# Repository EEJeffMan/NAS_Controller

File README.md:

# NAS_Controller
This is a PCB that serves as a controller for power supplies and provides power/reset control for a Pi-based NAS.

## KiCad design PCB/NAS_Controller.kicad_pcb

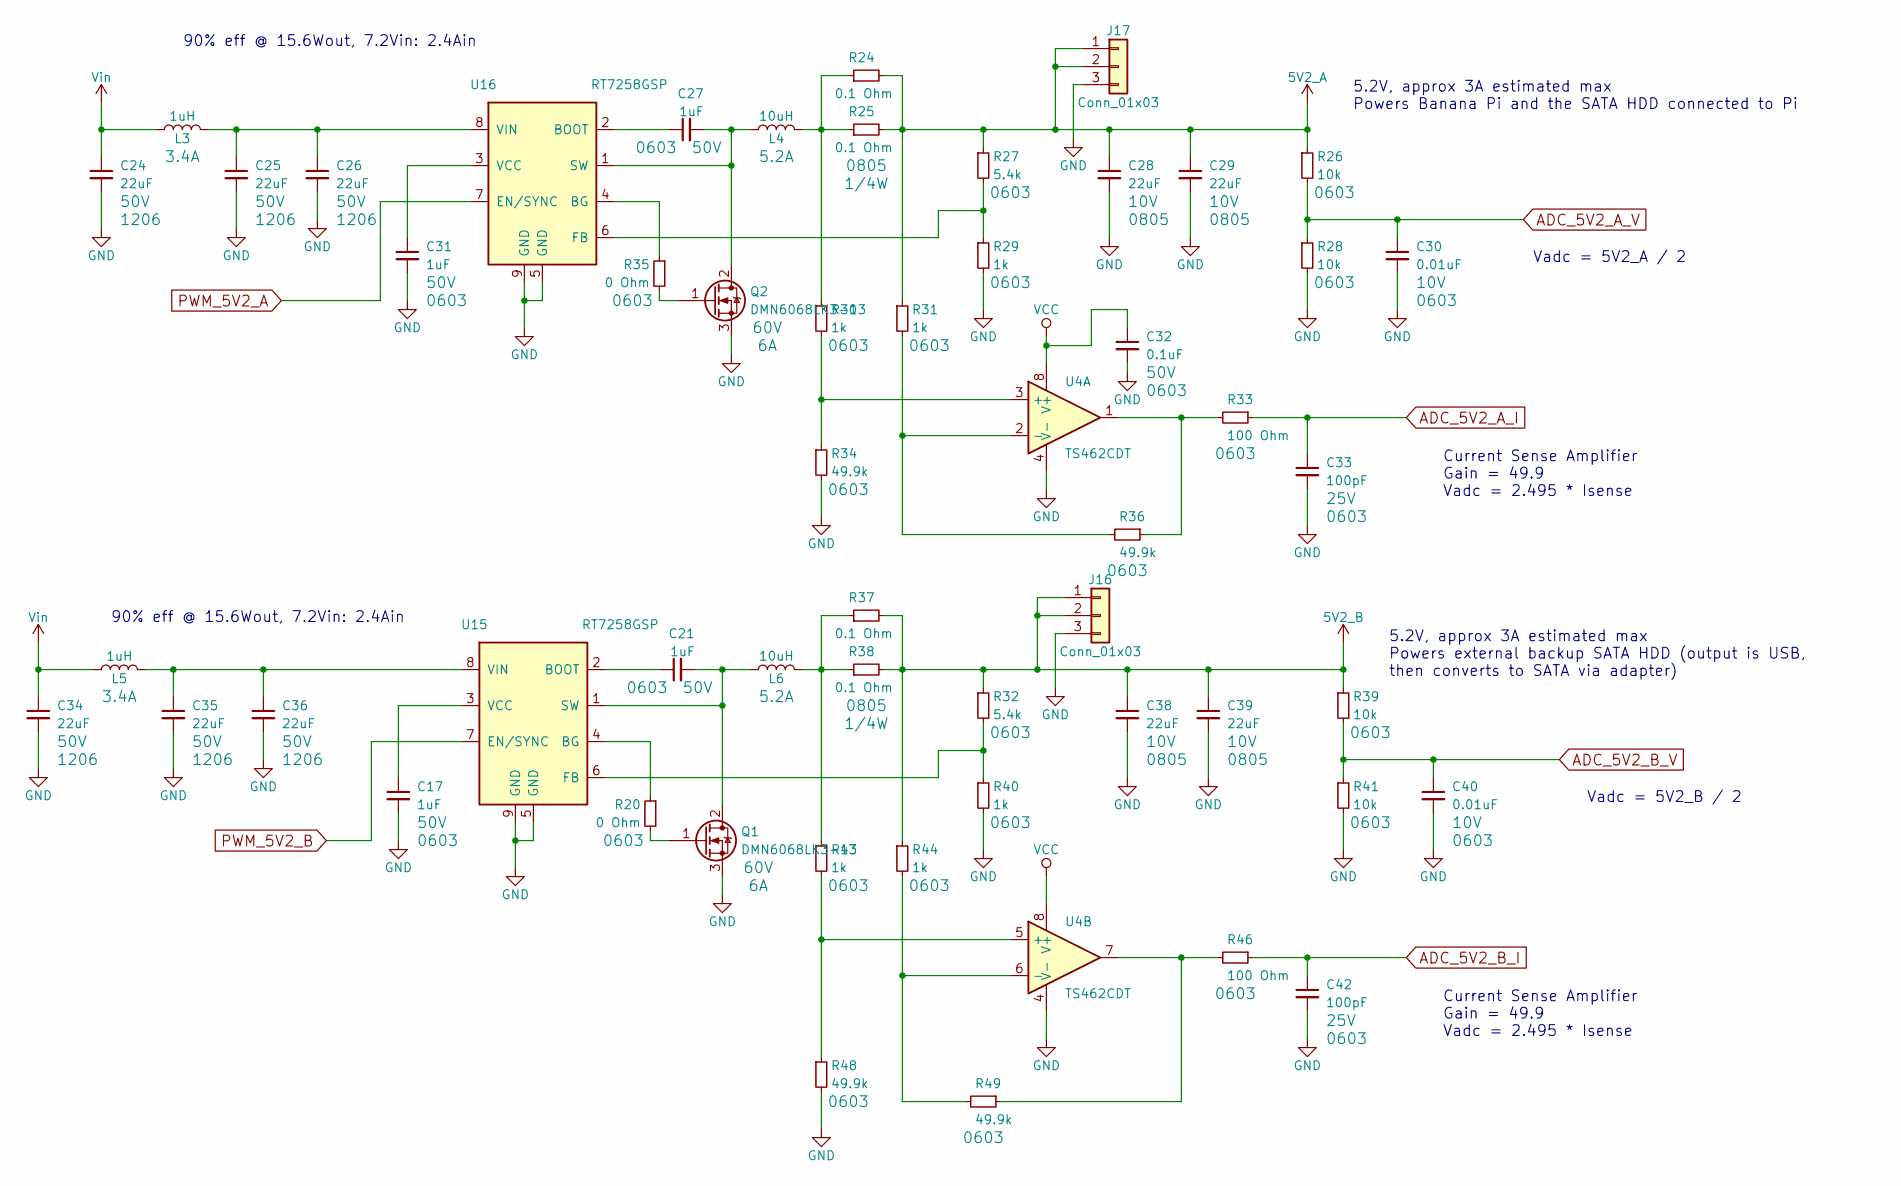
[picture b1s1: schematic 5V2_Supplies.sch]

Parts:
C17, C21, C27, C31: 1uF; C_0603; Voltage 50V
C24, C25, C26, C34, C35, C36: 22uF; C_1206; Voltage 50V
C28, C29, C38, C39: 22uF; C_0805; Voltage 10V
C30, C40: 0.01uF; C_0603; Voltage 10V
C32: 0.1uF; C_0603; Voltage 50V
C33, C42: 100pF; C_0603; Voltage 25V
J16, J17: Conn_01x03; Pin_Header_Straight_1x03_Pitch2.54mm_SMD_Pin1Right
L3, L5: 1uH; INDP2622X120N
L4, L6: 10uH; Inductor_Taiyo-Yuden_NR-80xx_HandSoldering
Q1, Q2: DMN6068LK3-13; TO-252-2; Voltage 60V
R20, R35: 0 Ohm; R_0603
R24, R25, R37, R38: 0.1 Ohm; R_0805
R26, R28, R39, R41: 10k; R_0603
R27, R32: 5.4k; R_0603
R29, R30, R31, R40, R43, R44: 1k; R_0603
R33, R46: 100 Ohm; R_0603
R34, R36, R48, R49: 49.9k; R_0603
U4: TS462CDT; SOIC-8_W3.9mm
U15, U16: RT7258GSP; SOIC-8-1EP_3.9x4.9mm_Pitch1.27mm_HandSoldering

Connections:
5V2_A: C28.1, C29.1, J17.1, J17.2, R24.2, R25.2, R26.1, R27.1, R31.1; also elsewhere on the board
5V2_B: C38.1, C39.1, J16.1, J16.2, R32.1, R37.2, R38.2, R39.1, R44.1; also elsewhere on the board
ADC_5V2_A_I: C33.1, R33.1; also elsewhere on the board
ADC_5V2_A_V: C30.1, R26.2, R28.1; also elsewhere on the board
ADC_5V2_B_I: C42.1, R46.1; also elsewhere on the board
ADC_5V2_B_V: C40.1, R39.2, R41.1; also elsewhere on the board
GND: C17.2, C24.2, C25.2, C26.2, C28.2, C29.2, C30.2, C31.2, C32.2, C33.2, C34.2, C35.2, C36.2, C38.2, C39.2, C40.2, C42.2, J16.3, J17.3, Q1.3 (S), Q2.3 (S), R28.2, R29.2, R34.2, R40.2, R41.2, R48.2, U4.4 (V-), U15.5 (GND), U15.9 (GND), U16.5 (GND), U16.9 (GND); also elsewhere on the board
unnamed: C17.1, U15.3 (VCC)
unnamed: C21.1, U15.2 (BOOT)
unnamed: C21.2, L6.1, Q1.2 (D), U15.1 (SW)
unnamed: C25.1, C26.1, L3.2, U16.8 (VIN)
unnamed: C27.1, U16.2 (BOOT)
unnamed: C27.2, L4.1, Q2.2 (D), U16.1 (SW)
unnamed: C31.1, U16.3 (VCC)
unnamed: C35.1, C36.1, L5.2, U15.8 (VIN)
unnamed: L4.2, R24.1, R25.1, R30.1
unnamed: L6.2, R37.1, R38.1, R43.1
unnamed: Q1.1 (G), R20.2
unnamed: Q2.1 (G), R35.2
unnamed: R20.1, U15.4 (BG)
unnamed: R27.2, R29.1, U16.6 (FB)
unnamed: R30.2, R34.1, U4.3 (+)
unnamed: R31.2, R36.2, U4.2 (-)
unnamed: R32.2, R40.1, U15.6 (FB)
unnamed: R33.2, R36.1, U4.1
unnamed: R35.1, U16.4 (BG)
unnamed: R43.2, R48.1, U4.5 (+)
unnamed: R44.2, R49.2, U4.6 (-)
unnamed: R46.2, R49.1, U4.7
PWM_5V2_A: U16.7 (EN/SYNC); also elsewhere on the board
PWM_5V2_B: U15.7 (EN/SYNC); also elsewhere on the board
VCC: C32.1, U4.8 (V+); also elsewhere on the board
Vin: C24.1, C34.1, L3.1, L5.1; also elsewhere on the board

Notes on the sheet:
5.2V, approx 3A estimated max Powers Banana Pi and the SATA HDD connected to Pi
Vadc = 5V2_A / 2
Current Sense Amplifier Gain = 49.9 Vadc = 2.495 * Isense
Vadc = 5V2_B / 2
5.2V, approx 3A estimated max Powers external backup SATA HDD (output is USB, then converts to SATA via adapter)
90% eff @ 15.6Wout, 7.2Vin: 2.4Ain

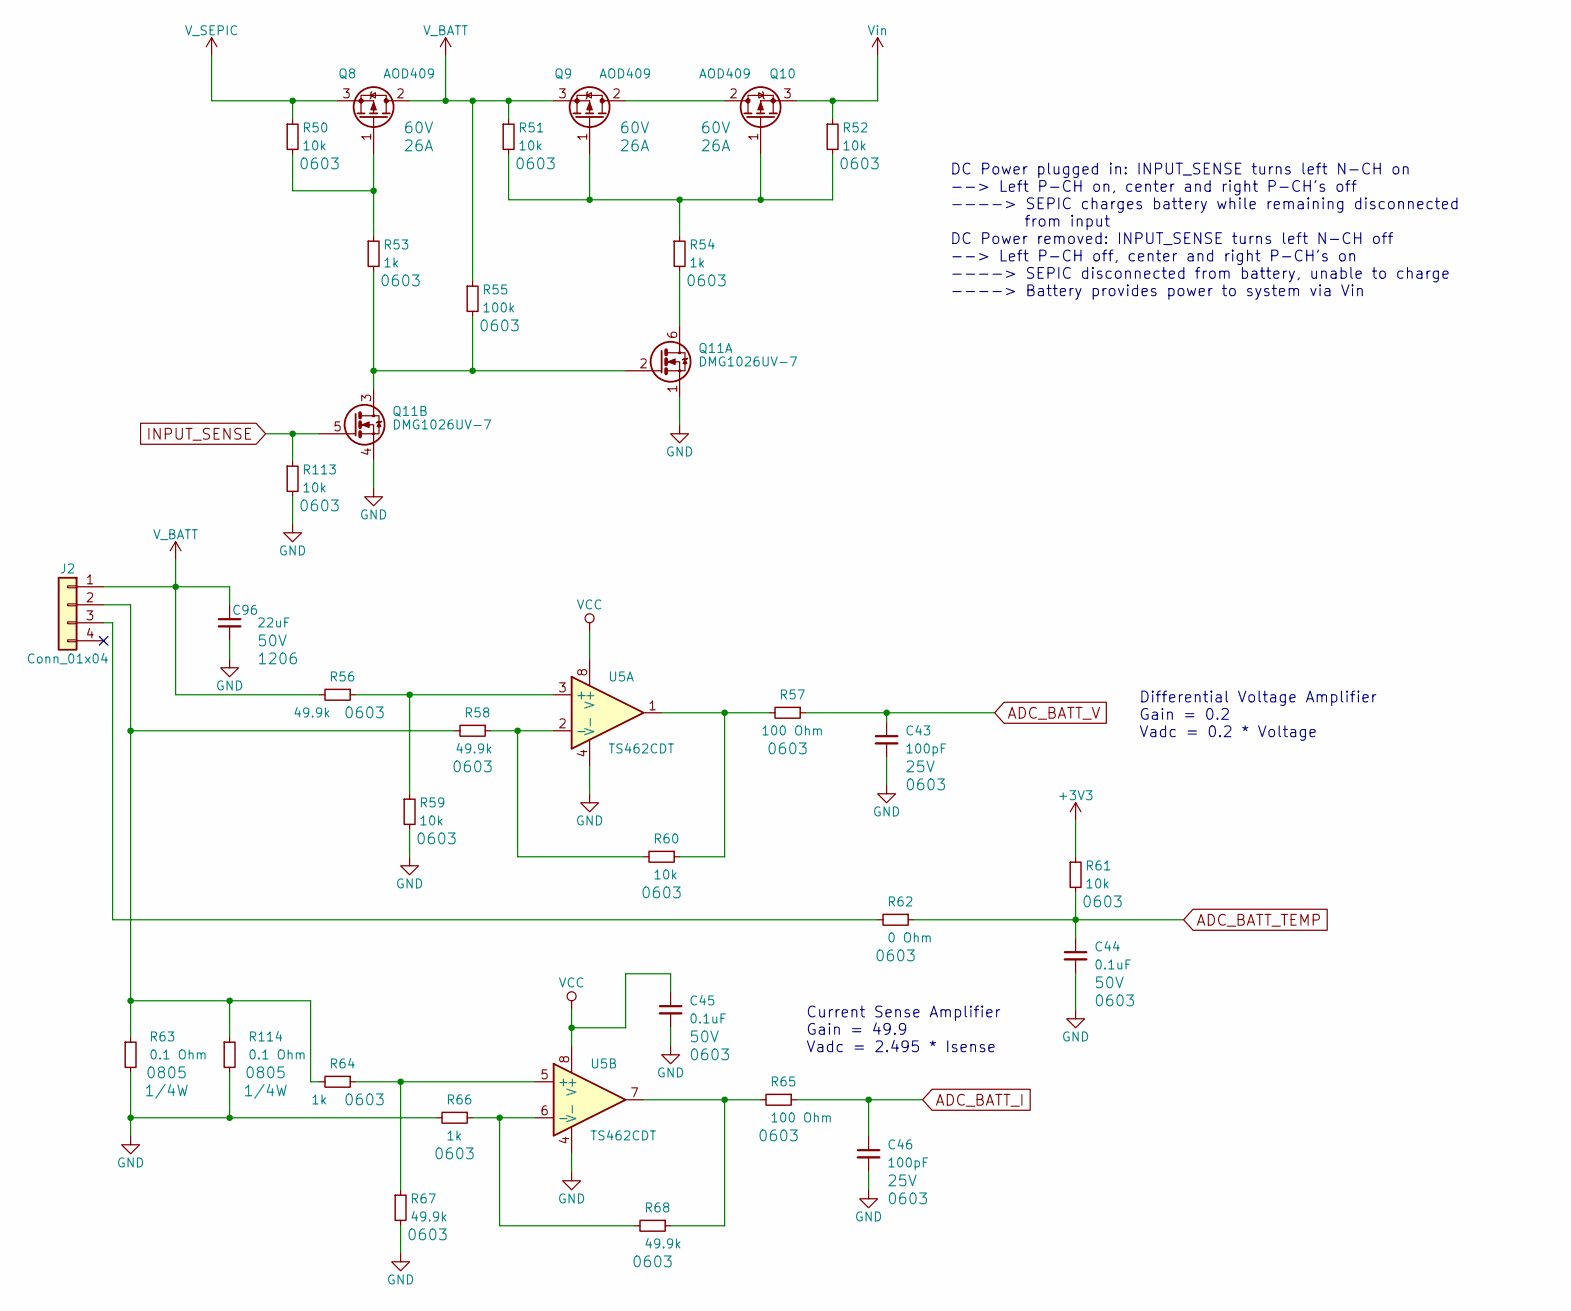
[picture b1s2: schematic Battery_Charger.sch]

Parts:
C43, C46: 100pF; C_0603; Voltage 25V
C44, C45: 0.1uF; C_0603; Voltage 50V
C96: 22uF; C_1206; Voltage 50V
J2: Conn_01x04; Molex_MiniFit-JR-5569-04A1_2x02x4.20mm_Angled
Q8, Q9, Q10: AOD409; TO-252-2; Voltage 60V
Q11: DMG1026UV-7; SOT-563
R50, R51, R52, R59, R60, R61, R113: 10k; R_0603
R53, R54, R64, R66: 1k; R_0603
R55: 100k; R_0603
R56, R58, R67, R68: 49.9k; R_0603
R57, R65: 100 Ohm; R_0603
R62: 0 Ohm; R_0603
R63, R114: 0.1 Ohm; R_0805
U5: TS462CDT; SOIC-8_W3.9mm

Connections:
+3V3: R61.1; also elsewhere on the board
ADC_BATT_I: C46.1, R65.1; also elsewhere on the board
ADC_BATT_TEMP: C44.1, R61.2, R62.1; also elsewhere on the board
ADC_BATT_V: C43.1, R57.1; also elsewhere on the board
GND: C43.2, C44.2, C45.2, C46.2, C96.2, Q11.1 (S), Q11.4 (S), R59.2, R63.2, R66.2, R67.2, R113.2, R114.2, U5.4 (V-); also elsewhere on the board
INPUT_SENSE: Q11.5 (G), R113.1; also elsewhere on the board
unnamed: J2.2, R58.2, R63.1, R64.2, R114.1
unnamed: J2.3, R62.2
unnamed: Q8.1 (G), R50.2, R53.1
unnamed: Q9.1 (G), Q10.1 (G), R51.2, R52.2, R54.1
unnamed: Q9.2 (D), Q10.2 (D)
unnamed: Q11.2 (G), Q11.3 (D), R53.2, R55.2
unnamed: Q11.6 (D), R54.2
unnamed: R56.1, R59.1, U5.3 (+)
unnamed: R57.2, R60.1, U5.1
unnamed: R58.1, R60.2, U5.2 (-)
unnamed: R64.1, R67.1, U5.5 (+)
unnamed: R65.2, R68.1, U5.7
unnamed: R66.1, R68.2, U5.6 (-)
VCC: C45.1, U5.8 (V+); also elsewhere on the board
V_BATT: C96.1, J2.1, Q8.2 (D), Q9.3 (S), R51.1, R55.1, R56.2
V_SEPIC: Q8.3 (S), R50.1; also elsewhere on the board
Vin: Q10.3 (S), R52.1; also elsewhere on the board

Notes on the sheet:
Current Sense Amplifier Gain = 49.9 Vadc = 2.495 * Isense
Differential Voltage Amplifier Gain = 0.2 Vadc = 0.2 * Voltage
DC Power plugged in: INPUT_SENSE turns left N-CH on --> Left P-CH on, center and right P-CH's off ----> SEPIC charges battery while remaining disconnected from input DC Power removed: INPUT_SENSE turns left N-CH off --> Left P-CH off, center and right P-CH's on ----> SEPIC disconnected from battery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

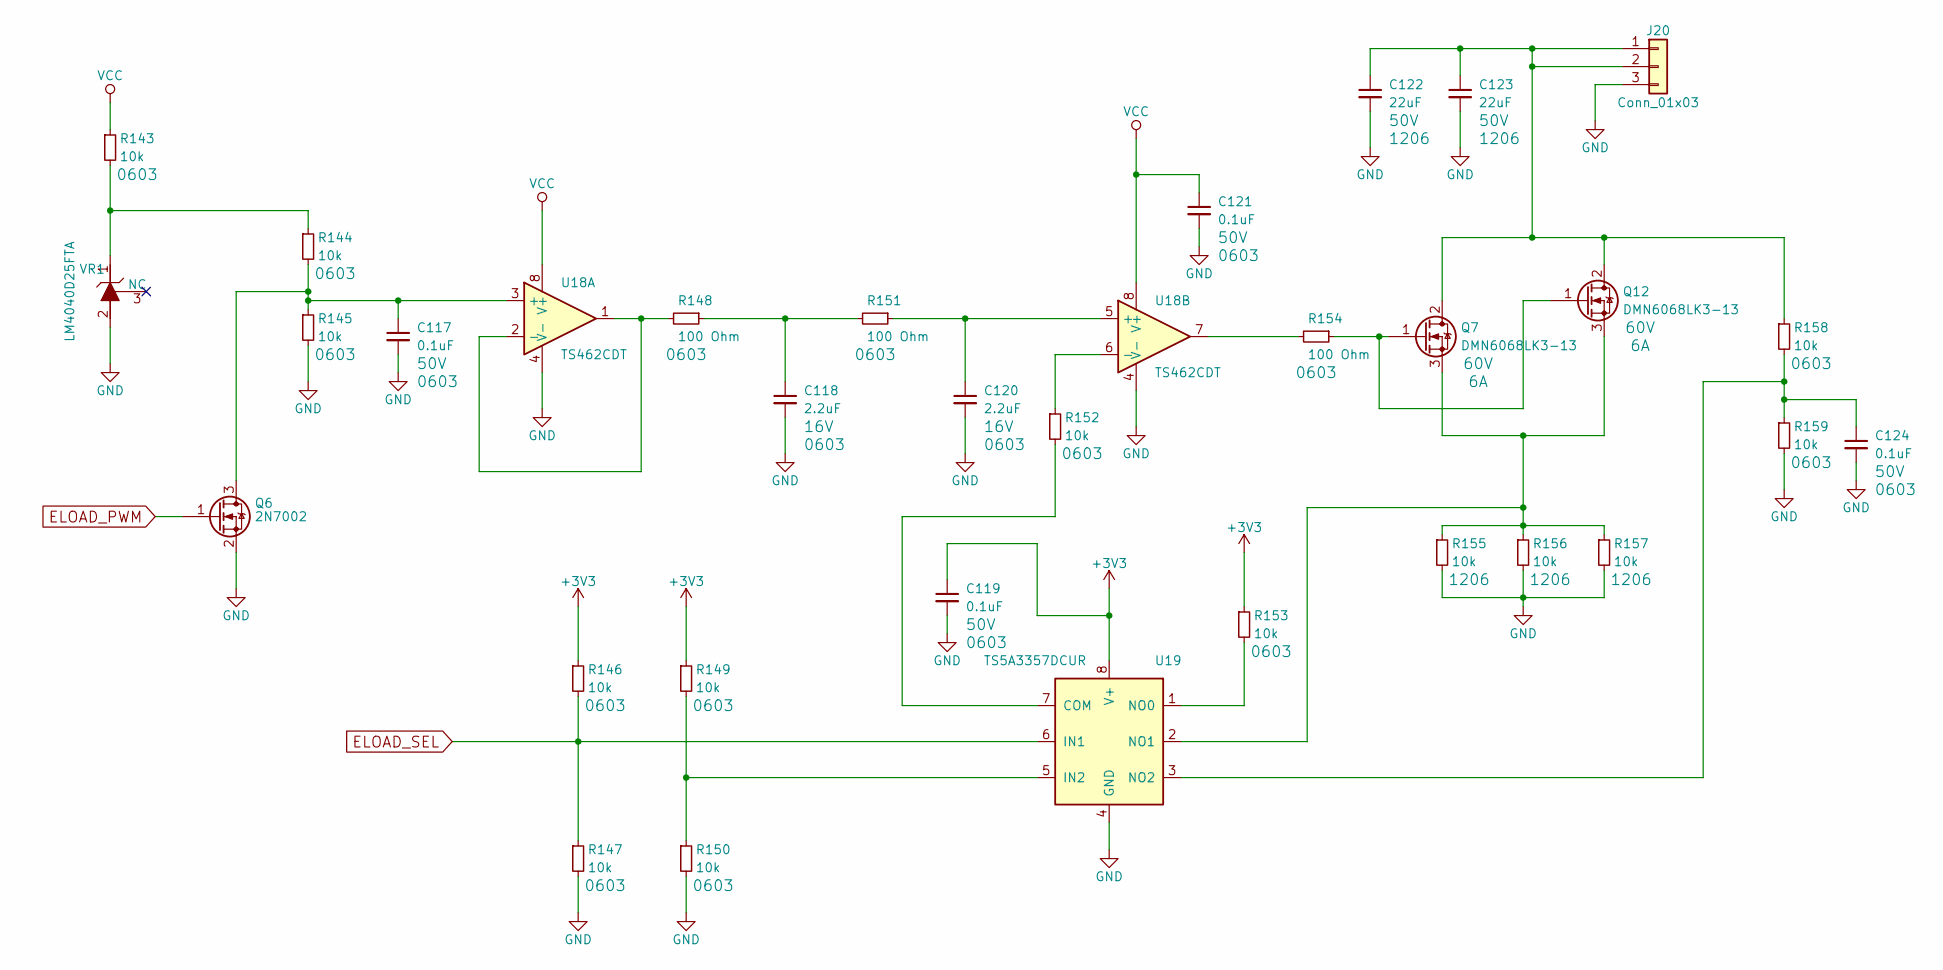
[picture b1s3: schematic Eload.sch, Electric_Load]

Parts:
C117, C119, C121, C124: 0.1uF; C_0603; Voltage 50V
C118, C120: 2.2uF; C_0603; Voltage 16V
C122, C123: 22uF; C_1206; Voltage 50V
J20: Conn_01x03; Pin_Header_Straight_1x03_Pitch2.54mm_SMD_Pin1Right
Q6: 2N7002; SOT-23
Q7, Q12: DMN6068LK3-13; TO-252-2; Voltage 60V
R143, R144, R145, R146, R147, R149, R150, R152, R153, R158, R159: 10k; R_0603
R148, R151, R154: 100 Ohm; R_0603
R155, R156, R157: 10k; R_1206
U18: TS462CDT; SOIC-8_W3.9mm
U19: TS5A3357DCUR; VSSOP-8_2.3x2mm_Pitch0.5mm
VR1: LM4040D25FTA; SOT-23-3; MPN LM4040D25FTA; Digi-Key_PN LM4040D25FCT-ND

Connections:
+3V3: C119.1, R146.1, R149.1, R153.1, U19.8 (V+); also elsewhere on the board
ELOAD_PWM: Q6.1 (G); also elsewhere on the board
ELOAD_SEL: R146.2, R147.1, U19.6 (IN1); also elsewhere on the board
GND: C117.2, C118.2, C119.2, C120.2, C121.2, C122.2, C123.2, C124.2, J20.3, Q6.2 (S), R145.2, R147.2, R150.2, R155.2, R156.2, R157.2, R159.2, U18.4 (V-), U19.4 (GND), VR1.2; also elsewhere on the board
unnamed: C117.1, Q6.3 (D), R144.2, R145.1, U18.3 (+)
unnamed: C118.1, R148.1, R151.2
unnamed 79: C120.1, R151.1, U18.5 (+); also elsewhere on the board
unnamed: C122.1, C123.1, J20.1, J20.2, Q7.2 (D), Q12.2 (D), R158.1
unnamed: C124.1, R158.2, R159.1, U19.3 (NO2)
unnamed: Q7.1 (G), Q12.1 (G), R154.1
unnamed: Q7.3 (S), Q12.3 (S), R155.1, R156.1, R157.1, U19.2 (NO1)
unnamed: R143.2, R144.1, VR1.1
unnamed: R148.2, U18.1, U18.2 (-)
unnamed: R149.2, R150.1, U19.5 (IN2)
unnamed: R152.1, U18.6 (-)
unnamed 181: R152.2, U19.7 (COM); also elsewhere on the board
unnamed: R153.2, U19.1 (NO0)
unnamed: R154.2, U18.7
VCC: C121.1, R143.1, U18.8 (V+); also elsewhere on the board

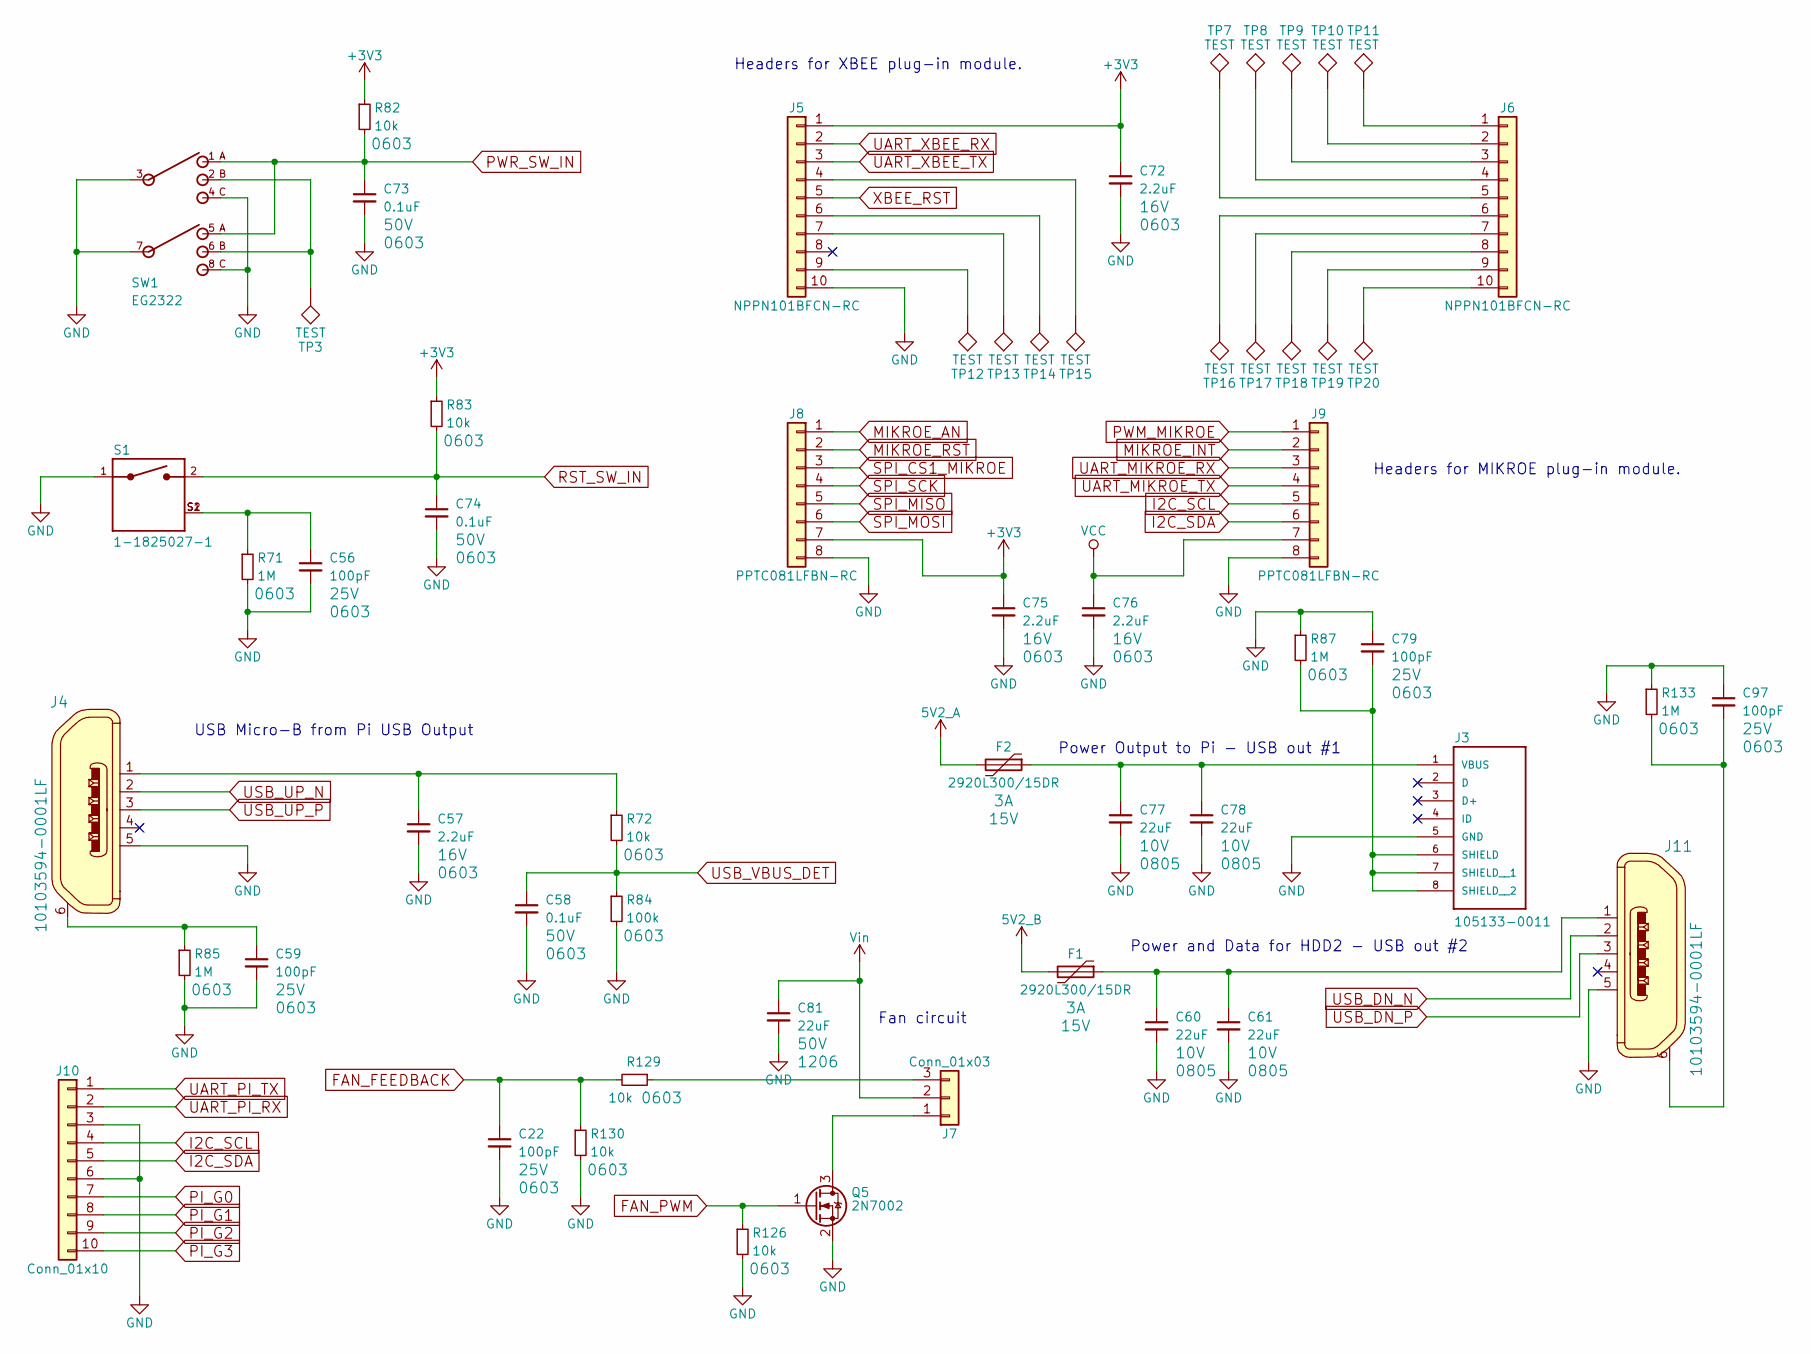
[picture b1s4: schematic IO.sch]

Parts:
C22, C56, C59, C79, C97: 100pF; C_0603; Voltage 25V
C57, C72, C75, C76: 2.2uF; C_0603; Voltage 16V
C58, C73, C74: 0.1uF; C_0603; Voltage 50V
C60, C61, C77, C78: 22uF; C_0805; Voltage 10V
C81: 22uF; C_1206; Voltage 50V
F1, F2: 2920L300/15DR; 2920L; Voltage 15V
J3: 105133-0011; MOLEX_105133-0011
J4, J11: 10103594-0001LF; USB_Micro-B_10103594-0001LF
J5, J6: NPPN101BFCN-RC; Socket_Strip_Straight_1x10_Pitch2.00mm
J7: Conn_01x03; Pin_Header_Straight_1x03_Pitch2.54mm
J8, J9: PPTC081LFBN-RC; Socket_Strip_Straight_1x08_Pitch2.54mm
J10: Conn_01x10; Pin_Header_Angled_1x10_Pitch2.54mm
Q5: 2N7002; SOT-23
R71, R85, R87, R133: 1M; R_0603
R72, R82, R83, R126, R129, R130: 10k; R_0603
R84: 100k; R_0603
S1: 1-1825027-1; SW_1-1825027-1
SW1: EG2322
TP3, TP7, TP8, TP9, TP10, TP11, TP12, TP13, TP14, TP15, TP16, TP17, TP18, TP19, TP20: TEST; Measurement_Point_Round-SMD-Pad_Small

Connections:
5V2_A: F2.2; also elsewhere on the board
5V2_B: F1.2; also elsewhere on the board
+3V3: C72.1, C75.1, J5.1, J8.7, R82.1, R83.1; also elsewhere on the board
FAN_FEEDBACK: C22.1, R129.2, R130.1; also elsewhere on the board
FAN_PWM: Q5.1 (G), R126.1; also elsewhere on the board
GND: C22.2, C56.2, C57.2, C58.2, C59.2, C60.2, C61.2, C72.2, C73.2, C74.2, C75.2, C76.2, C77.2, C78.2, C79.1, C81.2, C97.1, J3.5 (GND), J4.5, J5.10, J8.8, J9.8, J10.3, J10.6, J11.5, Q5.2 (S), R71.2, R84.2, R85.2, R87.1, R126.2, R130.2, R133.1, S1.1, SW1.3, SW1.4, SW1.7, SW1.8; also elsewhere on the board
I2C_SCL: J9.5, J10.4; also elsewhere on the board
I2C_SDA: J9.6, J10.5; also elsewhere on the board
MIKROE_AN: J8.1; also elsewhere on the board
MIKROE_INT: J9.2; also elsewhere on the board
MIKROE_RST: J8.2; also elsewhere on the board
unnamed: C56.1, R71.1, S1.S1 (SHIELD), S1.S2 (SHIELD)
unnamed: C57.1, J4.1, R72.1
unnamed: C59.1, J4.6, R85.1
unnamed: C60.1, C61.1, F1.1, J11.1
unnamed: C77.1, C78.1, F2.1, J3.1 (VBUS)
unnamed: C79.2, J3.6 (SHIELD), J3.7 (SHIELD__1), J3.8 (SHIELD__2), R87.2
unnamed: C97.2, J11.6, R133.2
unnamed: J5.4, TP15.1
unnamed: J5.6, TP14.1
unnamed: J5.7, TP13.1
unnamed: J5.9, TP12.1
unnamed: J6.1, TP11.1
unnamed: J6.2, TP10.1
unnamed: J6.3, TP9.1
unnamed: J6.4, TP8.1
unnamed: J6.5, TP7.1
unnamed: J6.6, TP16.1
unnamed: J6.7, TP17.1
unnamed: J6.8, TP18.1
unnamed: J6.9, TP19.1
unnamed: J6.10, TP20.1
unnamed: J7.1, Q5.3 (D)
unnamed: J7.3, R129.1
unnamed: SW1.2, SW1.6, TP3.1
PI_G0: J10.7; also elsewhere on the board
PI_G1: J10.8; also elsewhere on the board
PI_G2: J10.9; also elsewhere on the board
PI_G3: J10.10; also elsewhere on the board
PWM_MIKROE: J9.1; also elsewhere on the board
PWR_SW_IN: C73.1, R82.2, SW1.1, SW1.5; also elsewhere on the board
RST_SW_IN: C74.1, R83.2, S1.2; also elsewhere on the board
SPI_CS1_MIKROE: J8.3; also elsewhere on the board
SPI_MISO: J8.5; also elsewhere on the board
SPI_MOSI: J8.6; also elsewhere on the board
SPI_SCK: J8.4; also elsewhere on the board
UART_MIKROE_RX: J9.3; also elsewhere on the board
UART_MIKROE_TX: J9.4; also elsewhere on the board
UART_PI_RX: J10.2; also elsewhere on the board
UART_PI_TX: J10.1; also elsewhere on the board
UART_XBEE_RX: J5.2; also elsewhere on the board
UART_XBEE_TX: J5.3; also elsewhere on the board
USB_DN_N: J11.2; also elsewhere on the board
USB_DN_P: J11.3; also elsewhere on the board
USB_UP_N: J4.2; also elsewhere on the board
USB_UP_P: J4.3; also elsewhere on the board
USB_VBUS_DET: C58.1, R72.2, R84.1; also elsewhere on the board
VCC: C76.1, J9.7; also elsewhere on the board
Vin: C81.1, J7.2; also elsewhere on the board
XBEE_RST: J5.5; also elsewhere on the board

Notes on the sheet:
Headers for XBEE plug-in module.
Headers for MIKROE plug-in module.
Power Output to Pi - USB out #1
USB Micro-B from Pi USB Output
Power and Data for HDD2 - USB out #2
Fan circuit

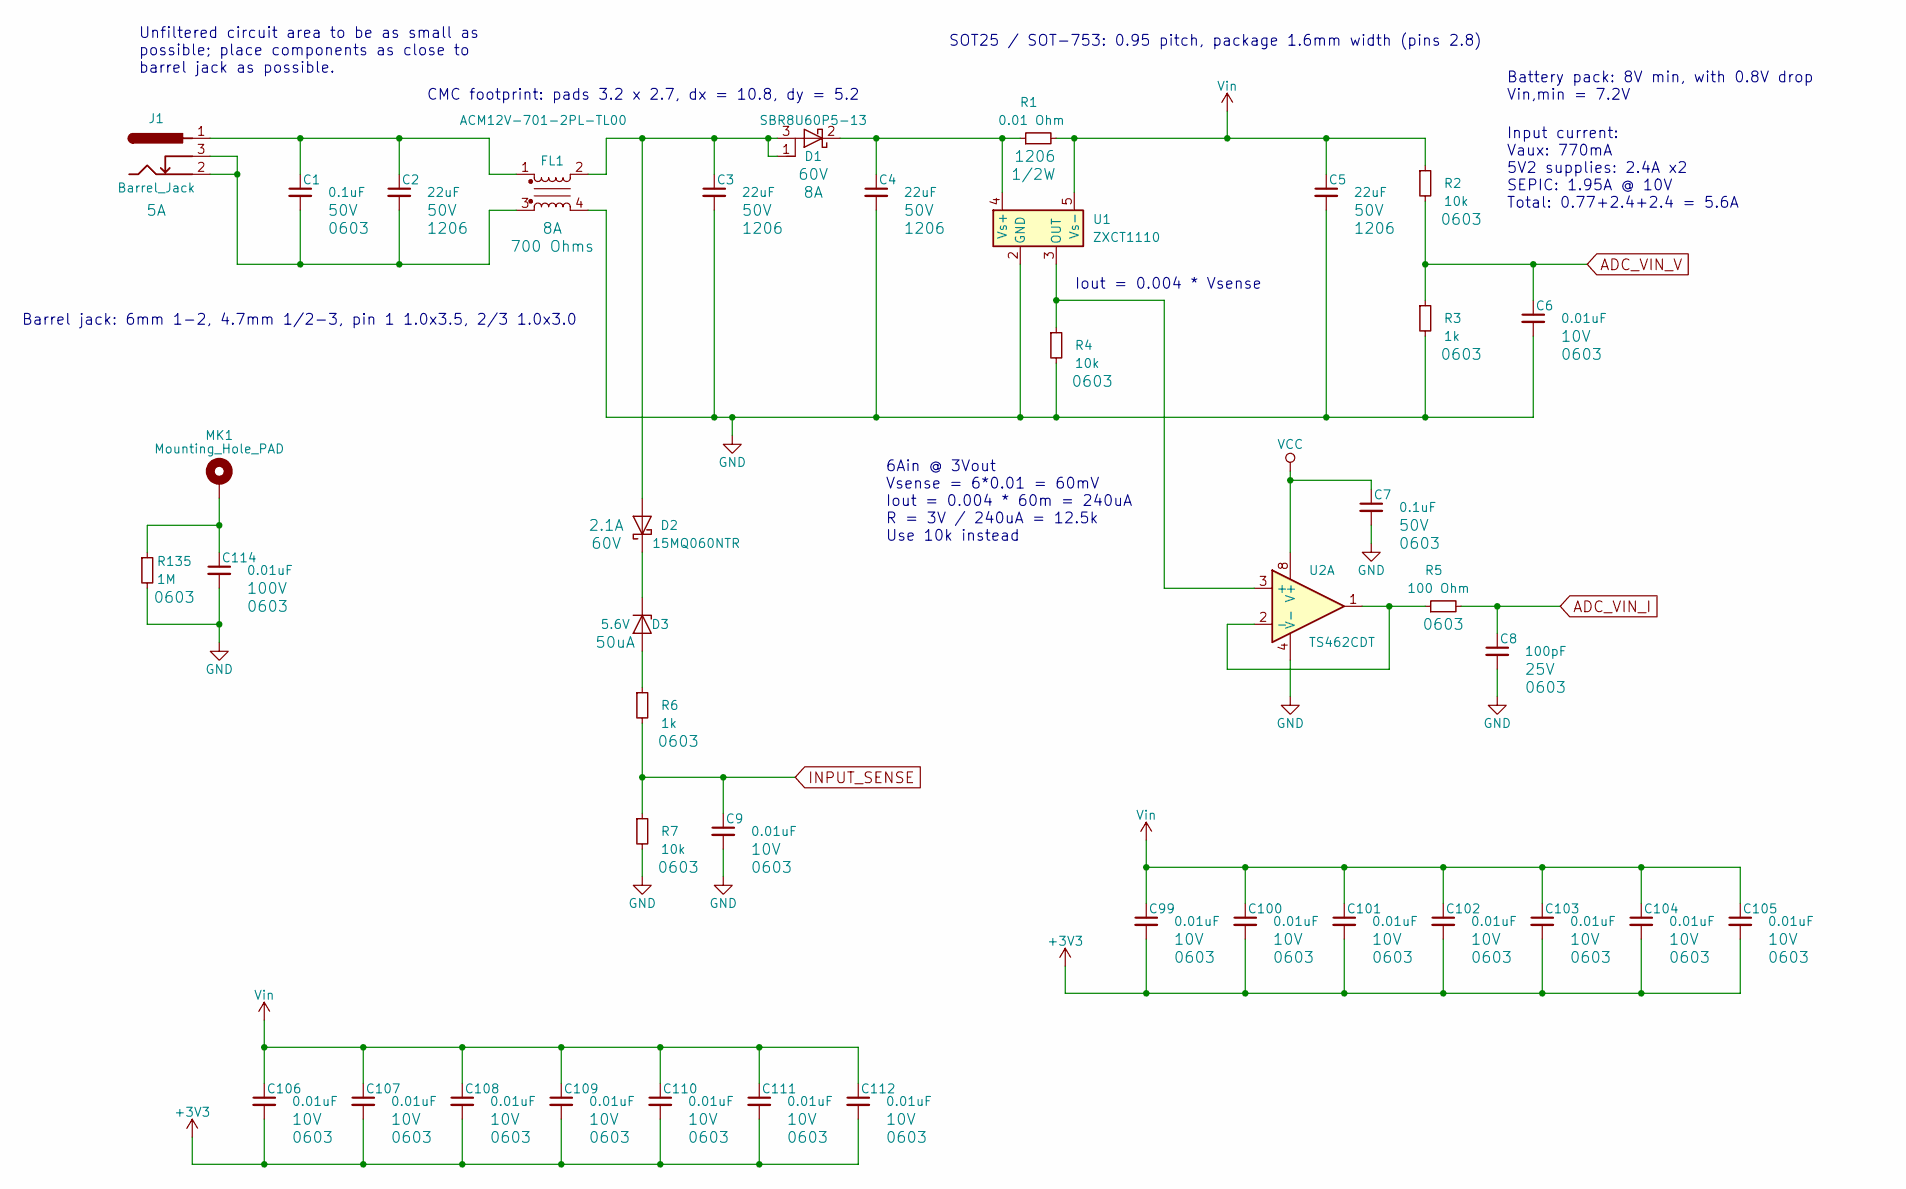
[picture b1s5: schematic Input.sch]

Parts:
C1, C7: 0.1uF; C_0603; Voltage 50V
C2, C3, C4, C5: 22uF; C_1206; Voltage 50V
C6, C9, C99, C100, C101, C102, C103, C104, C105, C106, C107, C108, C109, C110, C111, C112: 0.01uF; C_0603; Voltage 10V
C8: 100pF; C_0603; Voltage 25V
C114: 0.01uF; C_0603; Voltage 100V
D1: SBR8U60P5-13; Diodes_Incorporated_POWERDI_5; Voltage 60V
D2: 15MQ060NTR; D_SMA; Voltage 60V
D3: 5.6V; D_SOD-123
FL1: ACM12V-701-2PL-TL00; IND_ACM12V-701-2PL-TL00_FixedPadNumbers
J1: Barrel_Jack; BARREL_JACK
MK1: Mounting_Hole_PAD; MountingHole_4mm_Pad
R1: 0.01 Ohm; R_1206
R2, R4, R7: 10k; R_0603
R3, R6: 1k; R_0603
R5: 100 Ohm; R_0603
R135: 1M; R_0603
U1: ZXCT1110; SOT-753
U2: TS462CDT; SOIC-8_W3.9mm

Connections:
+3V3: C99.2, C100.2, C101.2, C102.2, C103.2, C104.2, C105.2, C106.2, C107.2, C108.2, C109.2, C110.2, C111.2, C112.2; also elsewhere on the board
ADC_VIN_I: C8.1, R5.2; also elsewhere on the board
ADC_VIN_V: C6.1, R2.2, R3.1; also elsewhere on the board
GND: C3.2, C4.2, C5.2, C6.2, C7.2, C8.2, C9.2, C114.2, FL1.4, R3.2, R4.2, R7.2, R135.2, U1.2 (GND), U2.4 (V-); also elsewhere on the board
INPUT_SENSE: C9.1, R6.2, R7.1; also elsewhere on the board
unnamed: C1.1, C2.1, FL1.1, J1.1
unnamed: C1.2, C2.2, FL1.3, J1.2, J1.3
unnamed: C3.1, D1.1 (A), D1.3 (A), D2.2 (A), FL1.2
unnamed: C4.1, D1.2 (K), R1.1, U1.4 (Vs+)
unnamed 74: C114.1, MK1.1, R135.1; also elsewhere on the board
unnamed: D2.1 (K), D3.1 (K)
unnamed: D3.2 (A), R6.1
unnamed: R4.1, U1.3 (OUT), U2.3 (+)
unnamed: R5.1, U2.1, U2.2 (-)
VCC: C7.1, U2.8 (V+); also elsewhere on the board
Vin: C5.1, C99.1, C100.1, C101.1, C102.1, C103.1, C104.1, C105.1, C106.1, C107.1, C108.1, C109.1, C110.1, C111.1, C112.1, R1.2, R2.1, U1.5 (Vs-); also elsewhere on the board

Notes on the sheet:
Unfiltered circuit area to be as small as possible; place components as close to barrel jack as possible.
Iout = 0.004 * Vsense
SOT25 / SOT-753: 0.95 pitch, package 1.6mm width (pins 2.8)
CMC footprint: pads 3.2 x 2.7, dx = 10.8, dy = 5.2
Barrel jack: 6mm 1-2, 4.7mm 1/2-3, pin 1 1.0x3.5, 2/3 1.0x3.0
6Ain @ 3Vout Vsense = 6*0.01 = 60mV Iout = 0.004 * 60m = 240uA R = 3V / 240uA = 12.5k Use 10k instead
Battery pack: 8V min, with 0.8V drop Vin,min = 7.2V
Input current: Vaux: 770mA 5V2 supplies: 2.4A x2 SEPIC: 1.95A @ 10V Total: 0.77+2.4+2.4 = 5.6A

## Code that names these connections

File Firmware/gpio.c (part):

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    EALLOW;
#ifdef PWM_ENABLE
    //--------------------------------------------------------------------------------------
    //  GPIO-00 - PIN FUNCTION = PWM1A (was Vaux, now TP2)
        GpioCtrlRegs.GPAMUX1.bit.GPIO0 = 1;     // 0=GPIO,  1=EPWM1A,  2=Resv,  3=Resv
    //  GpioCtrlRegs.GPADIR.bit.GPIO0 = 1;      // 1=OUTput,  0=INput
    //  GpioDataRegs.GPACLEAR.bit.GPIO0 = 1;    // uncomment if --> Set Low initially
    //  GpioDataRegs.GPASET.bit.GPIO0 = 1;      // uncomment if --> Set High initially
    //--------------------------------------------------------------------------------------
    //  GPIO-01 - PIN FUNCTION = ELOAD_PWM
        GpioCtrlRegs.GPAMUX1.bit.GPIO1 = 1;     // 0=GPIO,  1=EPWM1B,  2=Resv,  3=COMP1OUT
        GpioCtrlRegs.GPADIR.bit.GPIO1 = 1;      // 1=OUTput,  0=INput
        GpioDataRegs.GPACLEAR.bit.GPIO1 = 1;    // uncomment if --> Set Low initially
    //  GpioDataRegs.GPASET.bit.GPIO1 = 1;      // uncomment if --> Set High initially
#else
    //--------------------------------------------------------------------------------------
    //  GPIO-00 - PIN FUNCTION = PWM1A (Vaux)
        GpioCtrlRegs.GPAMUX1.bit.GPIO0 = 0;     // 0=GPIO,  1=EPWM1A,  2=Resv,  3=Resv
        GpioCtrlRegs.GPADIR.bit.GPIO0 = 0;      // 1=OUTput,  0=INput
    //  GpioDataRegs.GPACLEAR.bit.GPIO0 = 1;    // uncomment if --> Set Low initially
    //  GpioDataRegs.GPASET.bit.GPIO0 = 1;      // uncomment if --> Set High initially
    //--------------------------------------------------------------------------------------
    //  GPIO-01 - PIN FUNCTION = ELOAD_PWM
        GpioCtrlRegs.GPAMUX1.bit.GPIO1 = 0;     // 0=GPIO,  1=EPWM1B,  2=Resv,  3=COMP1OUT
        GpioCtrlRegs.GPADIR.bit.GPIO1 = 0;      // 1=OUTput,  0=INput
    //  GpioDataRegs.GPACLEAR.bit.GPIO1 = 1;    // uncomment if --> Set Low initially
    //  GpioDataRegs.GPASET.bit.GPIO1 = 1;      // uncomment if --> Set High initially
#endif
#ifdef PWM_ENABLE
    //--------------------------------------------------------------------------------------
    //  GPIO-02 - PIN FUNCTION = PWM2A (5V2_A)
        GpioCtrlRegs.GPAMUX1.bit.GPIO2 = 1;     // 0=GPIO,  1=EPWM2A,  2=Resv,  3=Resv
    //  GpioCtrlRegs.GPADIR.bit.GPIO2 = 0;      // 1=OUTput,  0=INput
    //  GpioDataRegs.GPACLEAR.bit.GPIO2 = 1;    // uncomment if --> Set Low initially
    //  GpioDataRegs.GPASET.bit.GPIO2 = 1;      // uncomment if --> Set High initially
#else
    //--------------------------------------------------------------------------------------
    //  GPIO-02 - PIN FUNCTION = PWM2A (5V2_A)
        GpioCtrlRegs.GPAMUX1.bit.GPIO2 = 0;     // 0=GPIO,  1=EPWM2A,  2=Resv,  3=Resv
        GpioCtrlRegs.GPADIR.bit.GPIO2 = 1;      // 1=OUTput,  0=INput
    //  GpioDataRegs.GPACLEAR.bit.GPIO2 = 1;    // uncomment if --> Set Low initially
        GpioDataRegs.GPASET.bit.GPIO2 = 1;      // uncomment if --> Set High initially
#endif
    //--------------------------------------------------------------------------------------
    //  GPIO-03 - PIN FUNCTION = Digital out (PI_RST_OUT)
        GpioCtrlRegs.GPAMUX1.bit.GPIO3 = 0;     // 0=GPIO,  1=EPWM2B,  2=SPISOMI-A,  3=COMP2OUT
        GpioCtrlRegs.GPADIR.bit.GPIO3 = 1;      // 1=OUTput,  0=INput
        GpioDataRegs.GPACLEAR.bit.GPIO3 = 1;    // uncomment if --> Set Low initially
    //  GpioDataRegs.GPASET.bit.GPIO3 = 1;      // uncomment if --> Set High initially
#ifdef PWM_ENABLE
    //--------------------------------------------------------------------------------------
    //  GPIO-04 - PIN FUNCTION = PWM3A (5V2_B)
        GpioCtrlRegs.GPAMUX1.bit.GPIO4 = 1;     // 0=GPIO,  1=EPWM3A,  2=Resv,  3=Resv
    //  GpioCtrlRegs.GPADIR.bit.GPIO4 = 0;      // 1=OUTput,  0=INput
    //  GpioDataRegs.GPACLEAR.bit.GPIO4 = 1;    // uncomment if --> Set Low initially
    //  GpioDataRegs.GPASET.bit.GPIO4 = 1;      // uncomment if --> Set High initially
#else
    //--------------------------------------------------------------------------------------
    //  GPIO-04 - PIN FUNCTION = PWM3A (5V2_B)
        GpioCtrlRegs.GPAMUX1.bit.GPIO4 = 0;     // 0=GPIO,  1=EPWM3A,  2=Resv,  3=Resv
        GpioCtrlRegs.GPADIR.bit.GPIO4 = 1;      // 1=OUTput,  0=INput
    //  GpioDataRegs.GPACLEAR.bit.GPIO4 = 1;    // uncomment if --> Set Low initially
        GpioDataRegs.GPASET.bit.GPIO4 = 1;      // uncomment if --> Set High initially
#endif
    //--------------------------------------------------------------------------------------
    //  GPIO-05 - PIN FUNCTION = Fan feedback (Ecap?)
        GpioCtrlRegs.GPAMUX1.bit.GPIO5 = 3;     // 0=GPIO,  1=EPWM3B,  2=SPISIMO-A,  3=ECAP1
    //  GpioCtrlRegs.GPADIR.bit.GPIO5 = 0;      // 1=OUTput,  0=INput
    //  GpioDataRegs.GPACLEAR.bit.GPIO5 = 1;    // uncomment if --> Set Low initially
    //  GpioDataRegs.GPASET.bit.GPIO5 = 1;      // uncomment if --> Set High initially
#ifdef PWM_ENABLE
    //--------------------------------------------------------------------------------------
    //  GPIO-06 - PIN FUNCTION = PWM4A (SEPIC)
        GpioCtrlRegs.GPAMUX1.bit.GPIO6 = 1;     // 0=GPIO,  1=EPWM4A,  2=SYNCI,  3=SYNCO
    //  GpioCtrlRegs.GPADIR.bit.GPIO6 = 0;      // 1=OUTput,  0=INput
    //  GpioDataRegs.GPACLEAR.bit.GPIO6 = 1;    // uncomment if --> Set Low initially
    //  GpioDataRegs.GPASET.bit.GPIO6 = 1;      // uncomment if --> Set High initially
#else
    //--------------------------------------------------------------------------------------
    //  GPIO-06 - PIN FUNCTION = PWM4A (SEPIC)
        GpioCtrlRegs.GPAMUX1.bit.GPIO6 = 0;     // 0=GPIO,  1=EPWM4A,  2=SYNCI,  3=SYNCO
        GpioCtrlRegs.GPADIR.bit.GPIO6 = 0;      // 1=OUTput,  0=INput
    //  GpioDataRegs.GPACLEAR.bit.GPIO6 = 1;    // uncomment if --> Set Low initially
    //  GpioDataRegs.GPASET.bit.GPIO6 = 1;      // uncomment if --> Set High initially
#endif
    //--------------------------------------------------------------------------------------
    //  GPIO-07 - PIN FUNCTION = DEBUG_UART_RX
        GpioCtrlRegs.GPAMUX1.bit.GPIO7 = 2;     // 0=GPIO,  1=EPWM4B,  2=SCIRX-A,  3=Resv
    //  GpioCtrlRegs.GPADIR.bit.GPIO7 = 1;      // 1=OUTput,  0=INput
    //  GpioDataRegs.GPACLEAR.bit.GPIO7 = 1;    // uncomment if --> Set Low initially
    //  GpioDataRegs.GPASET.bit.GPIO7 = 1;      // uncomment if --> Set High initially
    //--------------------------------------------------------------------------------------
    //  GPIO-08 - PIN FUNCTION = PWM5A (MIKROE)
        GpioCtrlRegs.GPAMUX1.bit.GPIO8 = 1;     // 0=GPIO,  1=EPWM5A,  2=Resv,  3=ADCSOC-A
    //  GpioCtrlRegs.GPADIR.bit.GPIO8 = 0;      // 1=OUTput,  0=INput
    //  GpioDataRegs.GPACLEAR.bit.GPIO8 = 1;    // uncomment if --> Set Low initially
    //  GpioDataRegs.GPASET.bit.GPIO8 = 1;      // uncomment if --> Set High initially
    //--------------------------------------------------------------------------------------
    //  GPIO-09 - PIN FUNCTION = Digital in (MIKROE AN)
        GpioCtrlRegs.GPAMUX1.bit.GPIO9 = 0;     // 0=GPIO,  1=EPWM5B,  2=LINTX-A,  3=Resv
        GpioCtrlRegs.GPADIR.bit.GPIO9 = 0;      // 1=OUTput,  0=INput
    //  GpioDataRegs.GPACLEAR.bit.GPIO9 = 1;    // uncomment if --> Set Low initially
    //  GpioDataRegs.GPASET.bit.GPIO9 = 1;      // uncomment if --> Set High initially
    //--------------------------------------------------------------------------------------
    //  GPIO-10 - PIN FUNCTION = Digital out (PI_PWR_OUT)
        GpioCtrlRegs.GPAMUX1.bit.GPIO10 = 0;    // 0=GPIO,  1=EPWM6A,  2=Resv,  3=ADCSOC-B
        GpioCtrlRegs.GPADIR.bit.GPIO10 = 1;     // 1=OUTput,  0=INput
        GpioDataRegs.GPACLEAR.bit.GPIO10 = 1;   // uncomment if --> Set Low initially
    //  GpioDataRegs.GPASET.bit.GPIO10 = 1;     // uncomment if --> Set High initially
#ifdef PWM_ENABLE
    //--------------------------------------------------------------------------------------
    //  GPIO-11 - PIN FUNCTION = PWM6B (Fan)
        GpioCtrlRegs.GPAMUX1.bit.GPIO11 = 1;    // 0=GPIO,  1=EPWM6B,  2=LINRX-A,  3=Resv
    //  GpioCtrlRegs.GPADIR.bit.GPIO11 = 0;     // 1=OUTput,  0=INput
    //  GpioDataRegs.GPACLEAR.bit.GPIO11 = 1;   // uncomment if --> Set Low initially
    //  GpioDataRegs.GPASET.bit.GPIO11 = 1;     // uncomment if --> Set High initially
#else
    //--------------------------------------------------------------------------------------
    //  GPIO-11 - PIN FUNCTION = PWM6B (Fan)
        GpioCtrlRegs.GPAMUX1.bit.GPIO11 = 0;    // 0=GPIO,  1=EPWM6B,  2=LINRX-A,  3=Resv
        GpioCtrlRegs.GPADIR.bit.GPIO11 = 0;     // 1=OUTput,  0=INput
    //  GpioDataRegs.GPACLEAR.bit.GPIO11 = 1;   // uncomment if --> Set Low initially
    //  GpioDataRegs.GPASET.bit.GPIO11 = 1;     // uncomment if --> Set High initially
#endif
    //--------------------------------------------------------------------------------------
    //  GPIO-12 - PIN FUNCTION = DEBUG_UART_TX
        GpioCtrlRegs.GPAMUX1.bit.GPIO12 = 2;    // 0=GPIO,  1=TZ1,  2=SCITX-A,  3=SPISIMO-B
    //  GpioCtrlRegs.GPADIR.bit.GPIO12 = 1;     // 1=OUTput,  0=INput
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
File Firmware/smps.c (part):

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
    /*
     * HWPWM pins:
     * GPIO1, 1B: PWM_ELOAD
     * GPIO2, 2A: PWM_5V2_A
     * GPIO4, 3A: PWM_5V2_B
     * GPIO6, 4A: PWM_SEPIC
     */
#ifdef PWM_ENABLE_ELOAD
    GpioCtrlRegs.GPAPUD.bit.GPIO1 = 1;    // Disable pull-up on GPIO1 (EPWM1B)
    GpioCtrlRegs.GPAMUX1.bit.GPIO1 = 1;   // Configure GPIO1 as EPWM1B
#endif
#ifdef PWM_ENABLE_5V2A
    GpioCtrlRegs.GPAPUD.bit.GPIO2 = 1;    // Disable pull-up on GPIO2 (EPWM2A)
    GpioCtrlRegs.GPAMUX1.bit.GPIO2 = 1;   // Configure GPIO2 as EPWM2A
#endif
#ifdef PWM_ENABLE_5V2B
    GpioCtrlRegs.GPAPUD.bit.GPIO4 = 1;    // Disable pull-up on GPIO4 (EPWM3A)
    GpioCtrlRegs.GPAMUX1.bit.GPIO4 = 1;   // Configure GPIO4 as EPWM3A
#endif
#ifdef PWM_ENABLE_SEPIC
    GpioCtrlRegs.GPAPUD.bit.GPIO6 = 1;    // Disable pull-up on GPIO6 (EPWM4A)
    GpioCtrlRegs.GPAMUX1.bit.GPIO6 = 1;   // Configure GPIO6 as EPWM4A
#endif
    /*
     * ePWM registers:
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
